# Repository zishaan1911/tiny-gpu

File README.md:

# Tiny GPU

A small triangle-rasterising GPU written in Verilog for the Lattice iCE40UP5K FPGA, plus the
4-layer board it would run on. A laptop sends triangles over USB, and the GPU fills them into
a framebuffer and drives a VGA monitor at 640×480, 60 Hz.

The board is a design only: it is fully routed and passes KiCad's checks, but it hasn't been
built.

## How it works

```
laptop ──USB──► FT2232H ──UART 1 Mbaud──► command FIFO ──► rasteriser ──► framebuffer ──► VGA
                                                                          64×64, 4-bit    640×480
```

- **Rasteriser** (`rtl/raster.v`): fills one pixel per clock using edge functions. Each edge
  steps by a single add per pixel, so the scan loop has no multipliers. Setup, which does
  need multiplies, is pipelined over seven clocks and runs on the FPGA's DSP blocks.
- **Framebuffer** (`rtl/framebuffer.v`): 64×64 pixels, 4 bits each, in block RAM. One port is
  for drawing and one for the display.
- **VGA** (`rtl/vga.v`): 640×480 at 60 Hz from a 25.125 MHz PLL clock. Each framebuffer
  pixel is drawn as a 7×7 block, giving a 448×448 picture centred on screen. A 16-colour
  palette feeds a 4-bit resistor DAC per channel.
- **Tear-free presenting:** `PRESENT` waits for vertical blank before it reports the frame
  done, so the host draws the next frame while the beam is off screen.
- **Host link** (`rtl/uart.v`, `rtl/cmd_port.v`): 8-byte commands at 1 Mbaud through a
  512-byte FIFO.

### Commands

Each command is 8 bytes: `0x55, op << 4 | colour, x0, y0, x1, y1, x2, y2`. Coordinates are
signed 8-bit, so vertices can sit off screen.

| op | Name     | What it does                                                    |
|----|----------|-----------------------------------------------------------------|
| 0  | CLEAR    | Fill the framebuffer with `colour`                              |
| 1  | TRIANGLE | Fill the triangle with `colour`                                 |
| 2  | PRESENT  | Wait for vertical blank, then reply `0x06`                      |

`host/spin.py` uses these to draw a spinning scene at 60 Hz.

### Results

- Both testbenches pass. `tb/tb.v` draws 48 frames on the core. `tb/tb_board.v` drives the
  whole design from its pins, as the laptop would over UART, then captures a VGA frame from
  the sync and colour pins and checks all 307,200 pixels.
- Synthesis uses 1,112 LUTs and 8 DSPs.
- Timing closes at 45.2 MHz against the 25.125 MHz needed.

## The board

76 × 56 mm, 4 layers (signal, ground, 3.3 V, signal):

- **iCE40UP5K** (QFN-48) with a 12 MHz oscillator and **W25Q128** configuration flash
- **FT2232H** USB bridge: channel A programs the flash, channel B carries the UART link
- **USB-C** power with ESD protection, **AMS1117** 3.3 V and **AP2112K** 1.2 V regulators
- **VGA** connector, fed by a 4-bit binary-weighted resistor DAC on each of red, green and blue

The board is generated from code. `pcb/gen/design.py` lists every part and net, and
`pcb/make_board.sh` turns it into the KiCad schematic and board:

1. Writes the schematic and runs ERC.
2. Places parts, sets up the stackup and drops a via from every ground and 3.3 V pad to its
   plane.
3. Autoroutes with Freerouting.
4. Finishes any nets Freerouting left with a small maze router that rips up and reroutes
   nearby nets (`pcb/gen/finish_routes.py`).
5. Adds ground pours and stitching vias, removes dangling stubs and fills zones.
6. Runs DRC with schematic parity and exports the schematic PDF.

The result has no unconnected pads and no clearance errors, and it matches the schematic.
The schematic is in [`pcb/tiny_gpu_schematic.pdf`](pcb/tiny_gpu_schematic.pdf).

## Building

Tools: Icarus Verilog, Yosys, nextpnr-ice40 and icestorm for the FPGA. For the board you need
KiCad 10, Java 17 with Freerouting 1.9, and Python with Pillow and NumPy for the renders. The
tool paths at the top of each script point at a Windows/MSYS2 setup, so change them to match
yours.

```bash
./build.sh               # simulate, synthesise, place and route, pack build/gpu.bin
./build.sh sim           # simulations only
pcb/make_board.sh        # regenerate, route and check the board
pcb/render_cinematic.sh  # cinematic renders (add "draft" for quick previews)
```

Freerouting doesn't route the same way every time, so a fresh `make_board.sh` run gives a
slightly different layout, which the finishing steps complete.

## Layout

```
rtl/        Verilog: rasteriser, framebuffer, GPU core, VGA, UART, command port, top level
tb/         testbenches for the core and the whole board
host/       Python driver for the laptop
board.pcf   FPGA pin map
pcb/        KiCad project, generator scripts, schematic PDF and renders
```

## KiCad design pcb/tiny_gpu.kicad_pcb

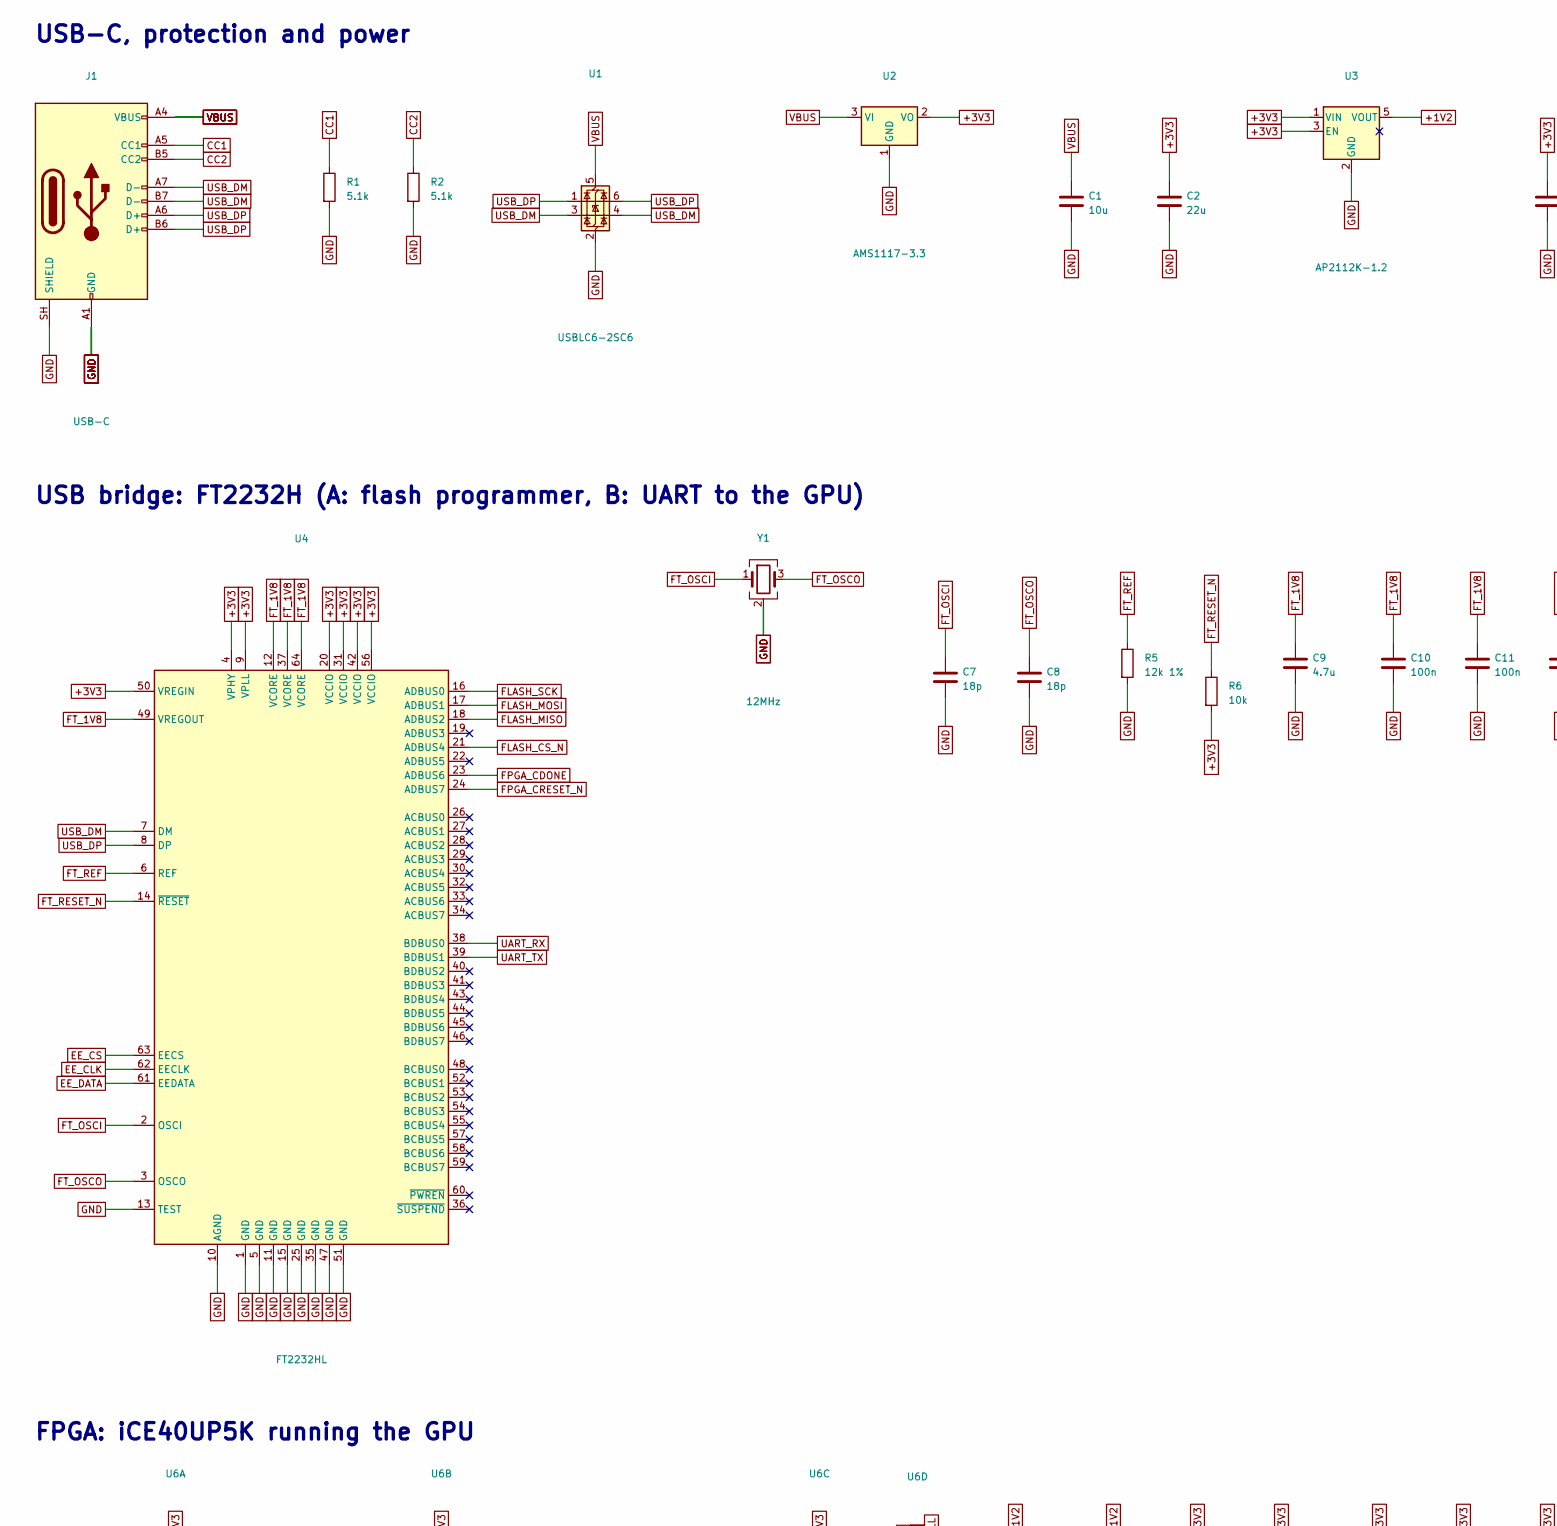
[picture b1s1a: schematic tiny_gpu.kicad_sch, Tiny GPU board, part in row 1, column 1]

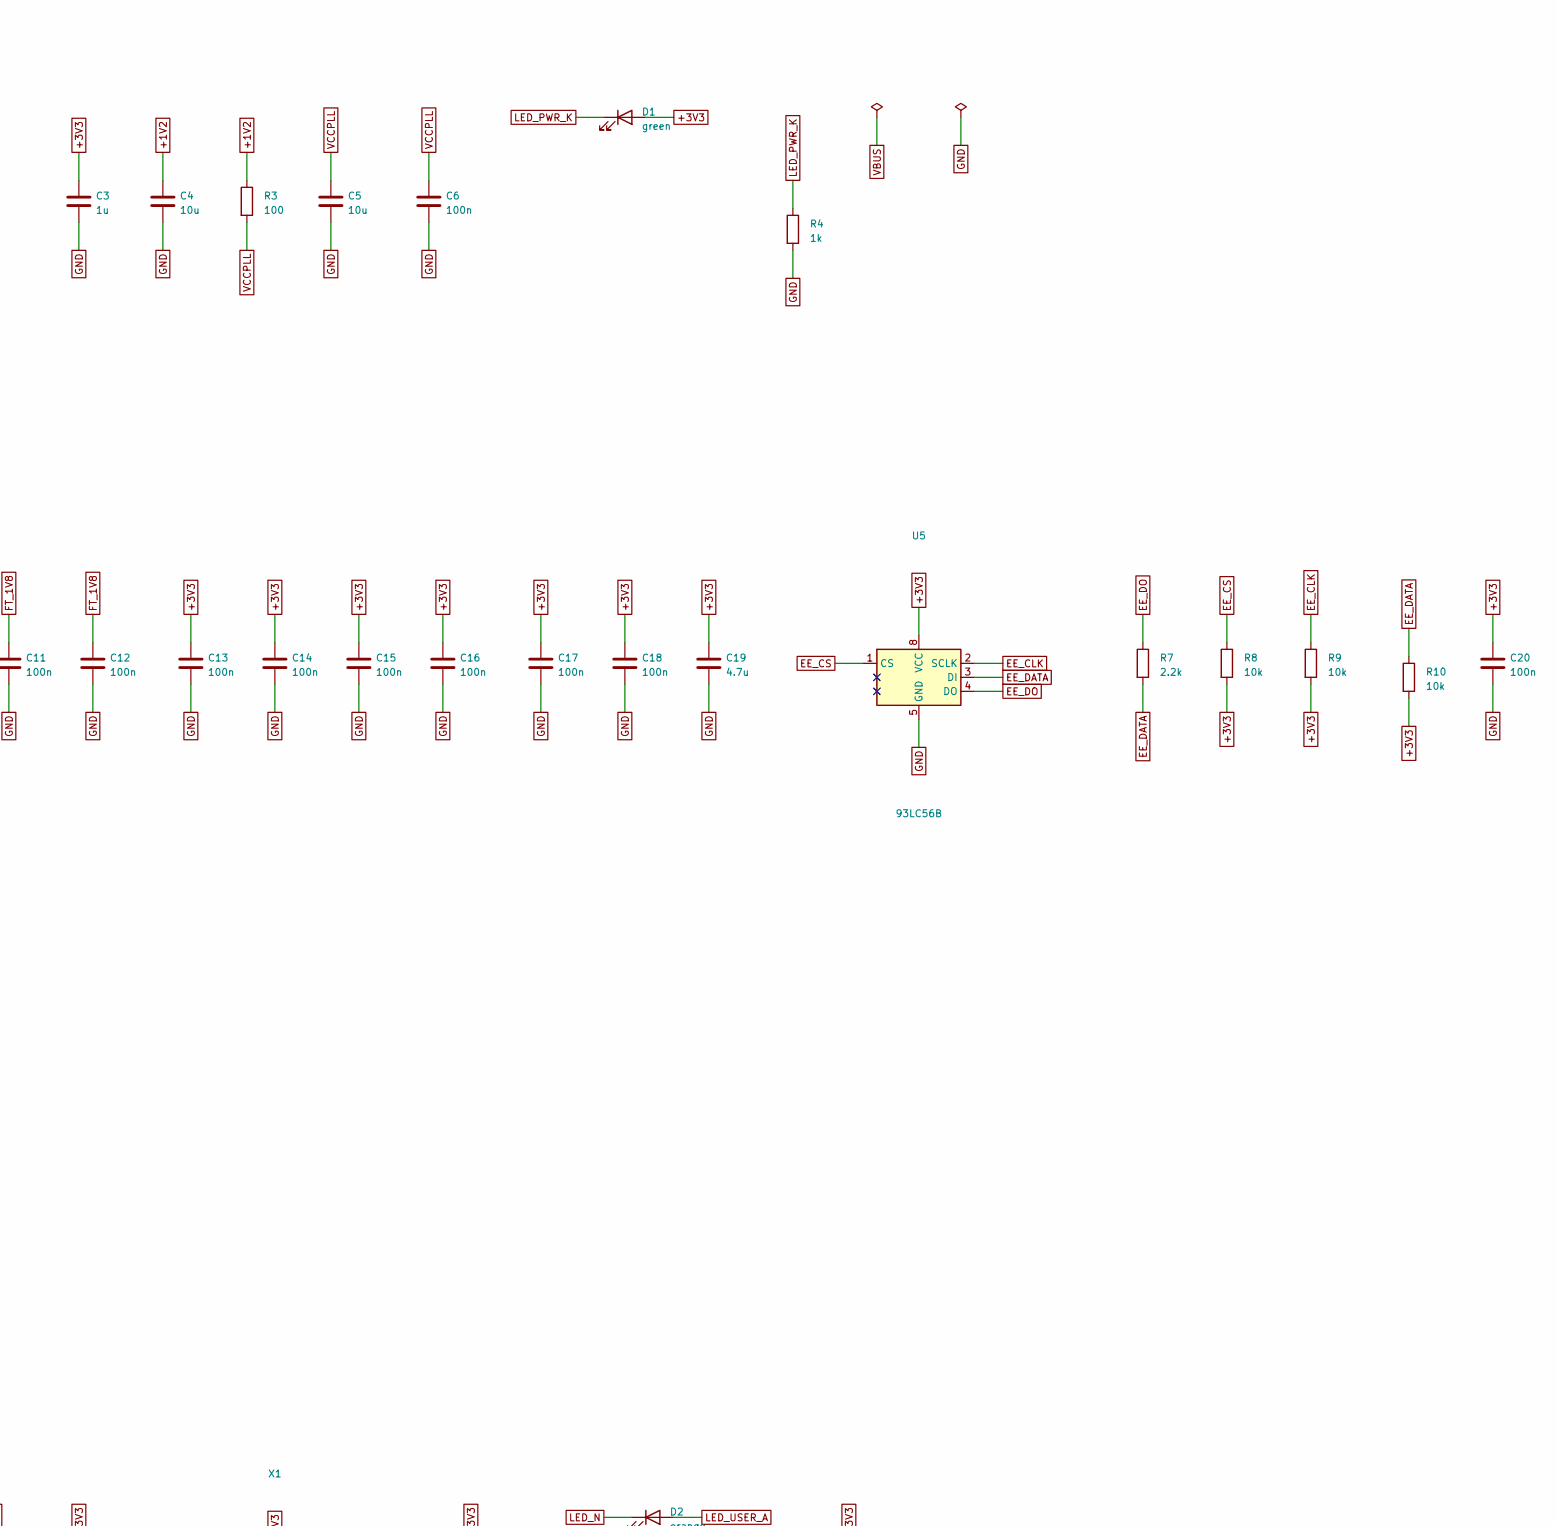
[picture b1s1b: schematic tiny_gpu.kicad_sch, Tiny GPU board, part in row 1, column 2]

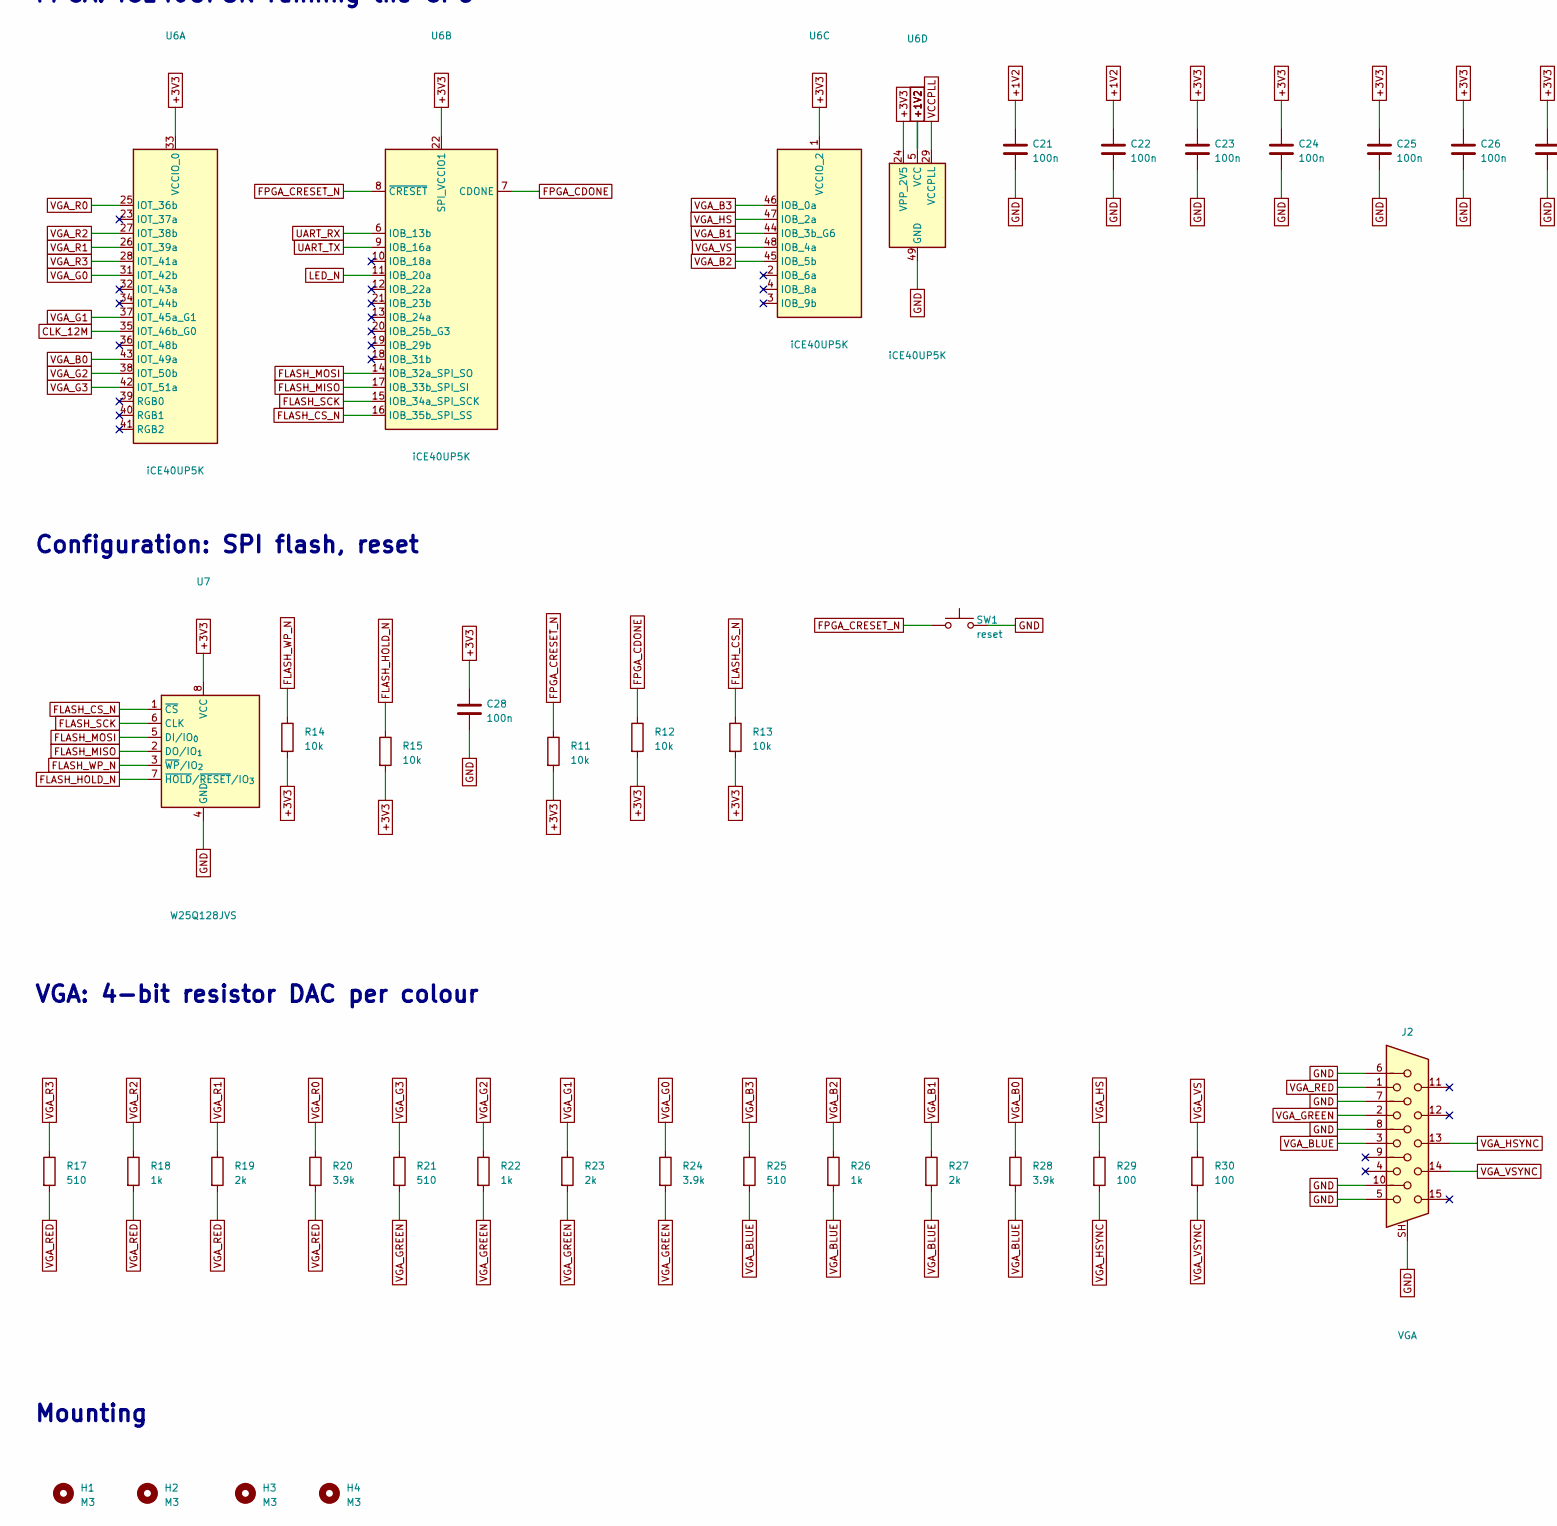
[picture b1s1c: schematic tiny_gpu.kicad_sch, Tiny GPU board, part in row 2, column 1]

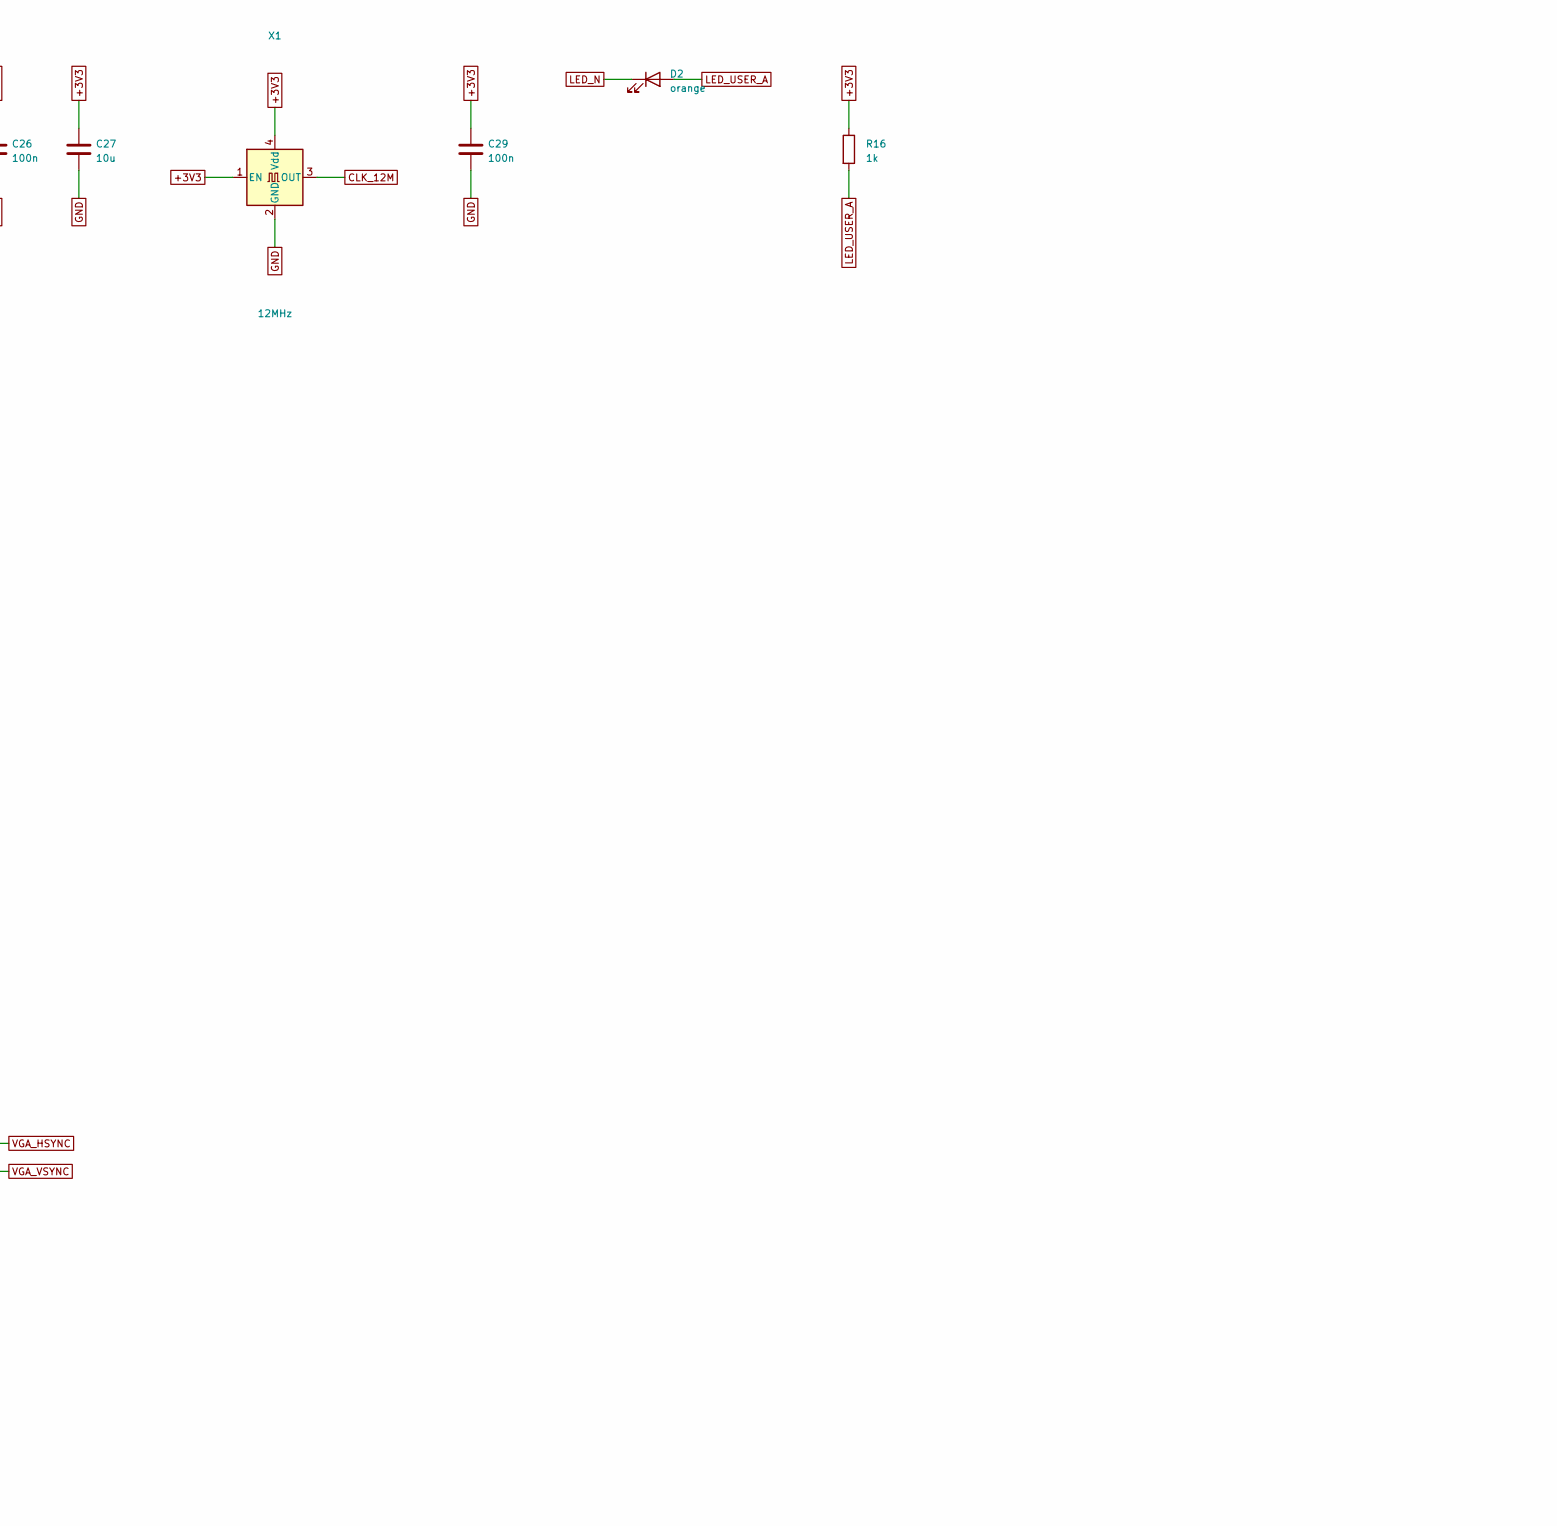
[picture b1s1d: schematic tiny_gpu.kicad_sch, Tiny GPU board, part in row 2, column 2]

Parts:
C1, C4, C5, C27: 10u; C_0805_2012Metric
C2: 22u; C_0805_2012Metric
C3: 1u; C_0603_1608Metric
C6, C10, C11, C12, C13, C14, C15, C16, C17, C18, C20, C21, C22, C23, C24, C25, C26, C28, C29: 100n; C_0603_1608Metric
C7, C8: 18p; C_0603_1608Metric
C9, C19: 4.7u; C_0805_2012Metric
D1: green; LED_0603_1608Metric
D2: orange; LED_0603_1608Metric
H1, H2, H3, H4: M3; MountingHole_3.2mm_M3
J1: USB-C; USB_C_Receptacle_HRO_TYPE-C-31-M-12; MPN HRO TYPE-C-31-M-12; LCSC C165948
J2: VGA; DSUB-15-HD_Socket_Horizontal_P2.29x1.90mm_EdgePinOffset3.03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; MPN DE-15 female, right angle, 3-row HD
R1, R2: 5.1k; R_0603_1608Metric
R3, R29, R30: 100; R_0603_1608Metric
R4, R16, R18, R22, R26: 1k; R_0603_1608Metric
R5: 12k 1%; R_0603_1608Metric
R6, R8, R9, R10, R11, R12, R13, R14, R15: 10k; R_0603_1608Metric
R7: 2.2k; R_0603_1608Metric
R17, R21, R25: 510; R_0603_1608Metric
R19, R23, R27: 2k; R_0603_1608Metric
R20, R24, R28: 3.9k; R_0603_1608Metric
SW1: reset; SW_SPST_TL3342; MPN TL3342F160QG
U1: USBLC6-2SC6; SOT-23-6; MPN USBLC6-2SC6; LCSC C7519
U2: AMS1117-3.3; SOT-223-3_TabPin2; MPN AMS1117-3.3; LCSC C6186
U3: AP2112K-1.2; SOT-23-5; MPN AP2112K-1.2TRG1
U4: FT2232HL; LQFP-64_10x10mm_P0.5mm; MPN FT2232HL-REEL
U5: 93LC56B; SOIC-8_3.9x4.9mm_P1.27mm; MPN 93LC56BT-I/SN
U6: iCE40UP5K; QFN-48-1EP_7x7mm_P0.5mm_EP5.6x5.6mm; MPN ICE40UP5K-SG48ITR
U7: W25Q128JVS; SOIC-8_5.3x5.3mm_P1.27mm; MPN W25Q128JVSIQ; LCSC C97521
X1: 12MHz; Oscillator_SMD_Abracon_ASE-4Pin_3.2x2.5mm; MPN ASE-12.000MHZ-LC-T
Y1: 12MHz; Crystal_SMD_3225-4Pin_3.2x2.5mm; MPN X322512MSB4SI; LCSC C9002

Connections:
+1V2: C4.1, C21.1, C22.1, R3.1, U3.5 (VOUT), U6.5 (VCC), U6.30 (VCC)
+3V3: C2.1, C3.1, C13.1, C14.1, C15.1, C16.1, C17.1, C18.1, C19.1, C20.1, C23.1, C24.1, C25.1, C26.1, C27.1, C28.1, C29.1, D1.2 (A), R6.2, R8.2, R9.2, R10.2, R11.2, R12.2, R13.2, R14.2, R15.2, R16.1, U2.2 (VO), U3.1 (VIN), U3.3 (EN), U4.4 (VPHY), U4.9 (VPLL), U4.20 (VCCIO), U4.31 (VCCIO), U4.42 (VCCIO), U4.50 (VREGIN), U4.56 (VCCIO), U5.8 (VCC), U6.1 (VCCIO_2), U6.22 (SPI_VCCIO1), U6.24 (VPP_2V5), U6.33 (VCCIO_0), U7.8 (VCC), X1.1 (EN), X1.4 (Vdd)
CC1: J1.A5 (CC1), R1.1
CC2: J1.B5 (CC2), R2.1
CLK_12M: U6.35 (IOT_46b_G0), X1.3 (OUT)
EE_CLK: R9.1, U4.62 (EECLK), U5.2 (SCLK)
EE_CS: R8.1, U4.63 (EECS), U5.1 (CS)
EE_DATA: R7.2, R10.1, U4.61 (EEDATA), U5.3 (DI)
EE_DO: R7.1, U5.4 (DO)
FLASH_CS_N: R13.1, U4.21 (ADBUS4), U6.16 (IOB_35b_SPI_SS), U7.1 (~CS)
FLASH_HOLD_N: R15.1, U7.7 (~HOLD/~RESET/IO_{3})
FLASH_MISO: U4.18 (ADBUS2), U6.17 (IOB_33b_SPI_SI), U7.2 (DO/IO_{1})
FLASH_MOSI: U4.17 (ADBUS1), U6.14 (IOB_32a_SPI_SO), U7.5 (DI/IO_{0})
FLASH_SCK: U4.16 (ADBUS0), U6.15 (IOB_34a_SPI_SCK), U7.6 (CLK)
FLASH_WP_N: R14.1, U7.3 (~WP/IO_{2})
FPGA_CDONE: R12.1, U4.23 (ADBUS6), U6.7 (CDONE)
FPGA_CRESET_N: R11.1, SW1.1, U4.24 (ADBUS7), U6.8 (~CRESET)
FT_1V8: C9.1, C10.1, C11.1, C12.1, U4.12 (VCORE), U4.37 (VCORE), U4.49 (VREGOUT), U4.64 (VCORE)
FT_OSCI: C7.1, U4.2 (OSCI), Y1.1
FT_OSCO: C8.1, U4.3 (OSCO), Y1.3
FT_REF: R5.1, U4.6 (REF)
FT_RESET_N: R6.1, U4.14 (~RESET)
GND: C1.2, C2.2, C3.2, C4.2, C5.2, C6.2, C7.2, C8.2, C9.2, C10.2, C11.2, C12.2, C13.2, C14.2, C15.2, C16.2, C17.2, C18.2, C19.2, C20.2, C21.2, C22.2, C23.2, C24.2, C25.2, C26.2, C27.2, C28.2, C29.2, J1.A1 (GND), J1.A12 (GND), J1.B1 (GND), J1.B12 (GND), J1.SH (SHIELD), J2.5, J2.6, J2.7, J2.8, J2.10, J2.SH, R1.2, R2.2, R4.2, R5.2, SW1.2, U1.2 (GND), U2.1 (GND), U3.2 (GND), U4.1 (GND), U4.5 (GND), U4.10 (AGND), U4.11 (GND), U4.13 (TEST), U4.15 (GND), U4.25 (GND), U4.35 (GND), U4.47 (GND), U4.51 (GND), U5.5 (GND), U6.49 (GND), U7.4 (GND), X1.2 (GND), Y1.2 (G), Y1.4 (G)
LED_N: D2.1 (K), U6.11 (IOB_20a)
LED_PWR_K: D1.1 (K), R4.1
LED_USER_A: D2.2 (A), R16.2
UART_RX: U4.38 (BDBUS0), U6.6 (IOB_13b)
UART_TX: U4.39 (BDBUS1), U6.9 (IOB_16a)
USB_DM: J1.A7 (D-), J1.B7 (D-), U1.3 (I/O2), U1.4 (I/O2), U4.7 (DM)
USB_DP: J1.A6 (D+), J1.B6 (D+), U1.1 (I/O1), U1.6 (I/O1), U4.8 (DP)
VBUS: C1.1, J1.A4 (VBUS), J1.A9 (VBUS), J1.B4 (VBUS), J1.B9 (VBUS), U1.5 (VBUS), U2.3 (VI)
VCCPLL: C5.1, C6.1, R3.2, U6.29 (VCCPLL)
VGA_B0: R28.1, U6.43 (IOT_49a)
VGA_B1: R27.1, U6.44 (IOB_3b_G6)
VGA_B2: R26.1, U6.45 (IOB_5b)
VGA_B3: R25.1, U6.46 (IOB_0a)
VGA_BLUE: J2.3, R25.2, R26.2, R27.2, R28.2
VGA_G0: R24.1, U6.31 (IOT_42b)
VGA_G1: R23.1, U6.37 (IOT_45a_G1)
VGA_G2: R22.1, U6.38 (IOT_50b)
VGA_G3: R21.1, U6.42 (IOT_51a)
VGA_GREEN: J2.2, R21.2, R22.2, R23.2, R24.2
VGA_HS: R29.1, U6.47 (IOB_2a)
VGA_HSYNC: J2.13, R29.2
VGA_R0: R20.1, U6.25 (IOT_36b)
VGA_R1: R19.1, U6.26 (IOT_39a)
VGA_R2: R18.1, U6.27 (IOT_38b)
VGA_R3: R17.1, U6.28 (IOT_41a)
VGA_RED: J2.1, R17.2, R18.2, R19.2, R20.2
VGA_VS: R30.1, U6.48 (IOB_4a)
VGA_VSYNC: J2.14, R30.2

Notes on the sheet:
USB-C, protection and power
USB bridge: FT2232H (A: flash programmer, B: UART to the GPU)
FPGA: iCE40UP5K running the GPU
Configuration: SPI flash, reset
VGA: 4-bit resistor DAC per colour
Mounting

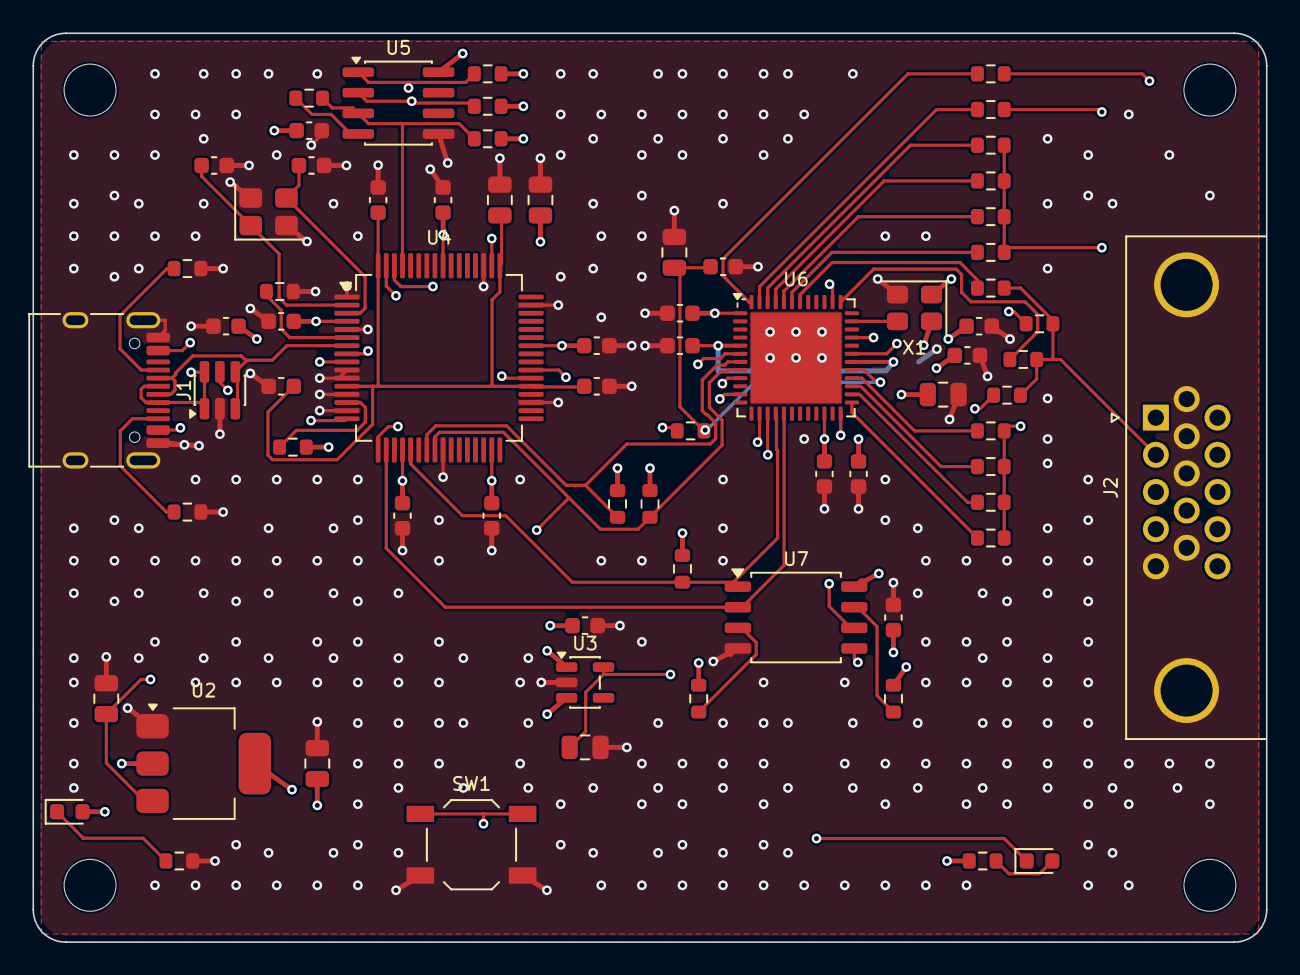
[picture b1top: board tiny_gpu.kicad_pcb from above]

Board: 4 copper layers, 76.0 x 56.0 mm, 77 parts (1 on the bottom side), 51 nets.

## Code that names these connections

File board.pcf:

# iCE40UP5K-SG48 pin map for the Tiny GPU board. Generated from pcb/gen/design.py (FPGA_PINS):
# the PCB is wired from the same table, so change pins there, not here.
set_io clk_12m    35
set_io uart_rx    6
set_io uart_tx    9
set_io led_n      11
set_io vga_r[0]   25
set_io vga_r[1]   26
set_io vga_r[2]   27
set_io vga_r[3]   28
set_io vga_g[0]   31
set_io vga_g[1]   37
set_io vga_g[2]   38
set_io vga_g[3]   42
set_io vga_b[0]   43
set_io vga_b[1]   44
set_io vga_b[2]   45
set_io vga_b[3]   46
set_io vga_hs     47
set_io vga_vs     48
